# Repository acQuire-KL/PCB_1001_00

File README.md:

HISTORY

<table>
  <tr>
    <td valign="top">
      
    </td>
    <td valign="top">
      <table border="1">
        <tr>
          <th style="font-size: 14px; font-weight: bold;">VTPN</th>
          <th style="font-size: 14px; font-weight: bold;">Date</th>
          <th style="font-size: 14px; font-weight: bold;">Comments</th>
        </tr>
        <tr>
          <td style="font-size: 12px;">PCB_1001_02</td>
          <td style="font-size: 12px;">2025-04-02</td>
          <td style="font-size: 12px;">01 --> 02 rerouted to indepent circuits</td>
        </tr>
        <tr>
          <td style="font-size: 12px;">PCB_1001_01</td>
          <td style="font-size: 12px;">2025-03-28</td>
          <td style="font-size: 12px;">00 --> 01 to add new circuit sections</td>
        </tr>
        <tr>
          <td style="font-size: 12px;">PCB_1001_00</td>
          <td style="font-size: 12px;">2025-03-01</td>
          <td style="font-size: 12px;">Initial release</td>
        </tr>
      </table>
    </td>
  </tr>
</table>

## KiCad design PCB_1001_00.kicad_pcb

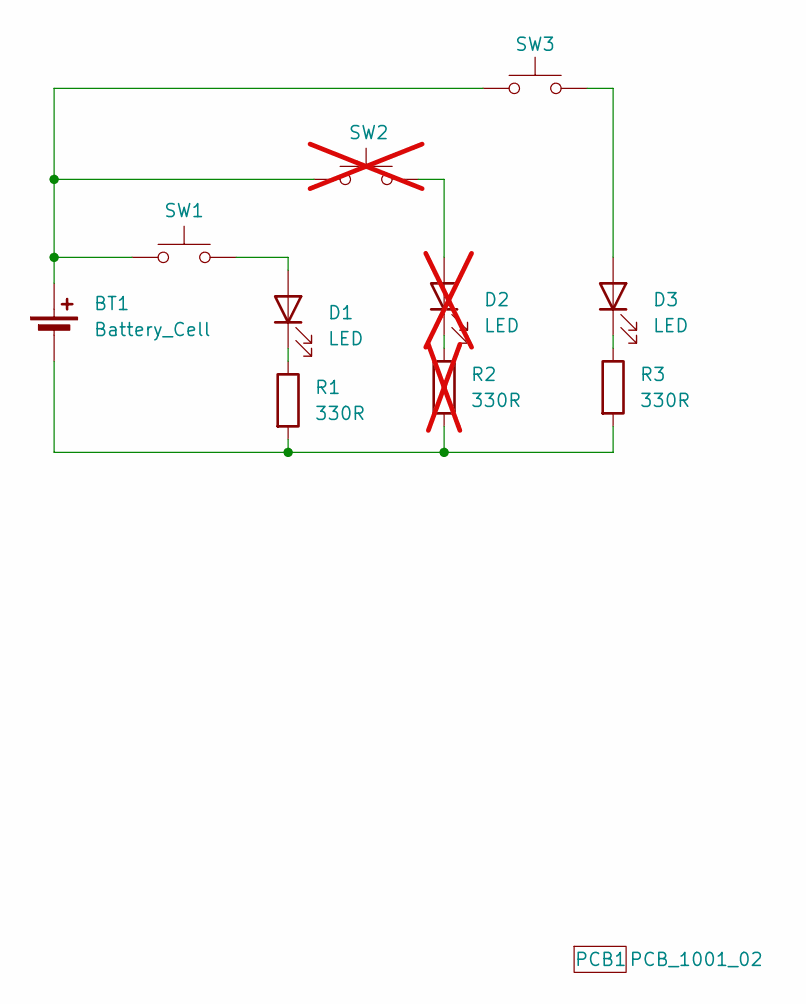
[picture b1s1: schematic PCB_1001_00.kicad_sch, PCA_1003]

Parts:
BT1: Battery_Cell; BatteryHolder_Keystone_1060_1x2032
D1, D3: LED; LED_0603_1608Metric
D2: LED; LED_0603_1608Metric; not fitted
PCB1: PCB_1001_02
R1, R3: 330R; R_0603_1608Metric
R2: 330R; R_0603_1608Metric; not fitted
SW1, SW3: SW_MEC_5G_edit; SW_Tactile_SPST_NO_Straight_CK_PTS636Sx25SMTRLFS
SW2: SW_MEC_5G_edit; SW_Tactile_SPST_NO_Straight_CK_PTS636Sx25SMTRLFS; not fitted

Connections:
unnamed: BT1.1 (+), SW1.1 (A), SW2.1 (A), SW3.1 (A)
unnamed: BT1.2 (-), R1.2, R2.2, R3.2
unnamed: D1.2 (A), SW1.2 (B)
unnamed: D1.1 (K), R1.1
unnamed: D2.2 (A), SW2.2 (B)
unnamed: D2.1 (K), R2.1
unnamed: D3.2 (A), SW3.2 (B)
unnamed: D3.1 (K), R3.1

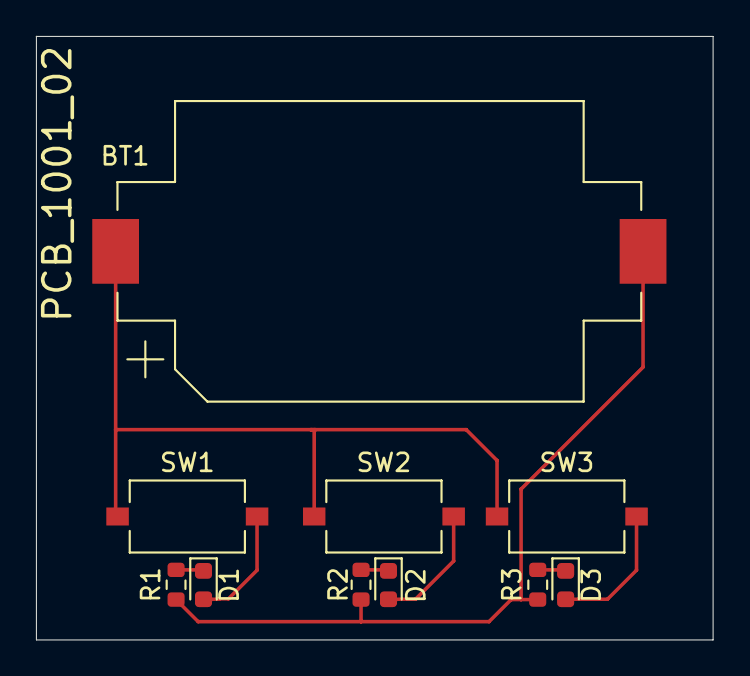
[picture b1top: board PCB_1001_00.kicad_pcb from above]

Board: 2 copper layers, 37.6 x 33.5 mm, 10 parts (0 on the bottom side), 8 nets.

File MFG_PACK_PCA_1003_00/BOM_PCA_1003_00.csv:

"Reference","Value","Datasheet","Footprint","Qty","DNP"
"BT1","Battery_Cell","~","Battery:BatteryHolder_Keystone_1060_1x2032","1",""
"D1,D3","LED","~","LED_SMD:LED_0603_1608Metric","2",""
"D2","LED","~","LED_SMD:LED_0603_1608Metric","1","DNP"
"R1,R3","330R","~","Resistor_SMD:R_0603_1608Metric","2",""
"R2","330R","~","Resistor_SMD:R_0603_1608Metric","1","DNP"
"SW1,SW3","SW_MEC_5G_edit","http://www.apem.com/int/index.php?controller=attachment&id_a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","Button_Switch_SMD:SW_Tactile_SPST_NO_Straight_CK_PTS636Sx25SMTRLFS","2",""
"SW2","SW_MEC_5G_edit","http://www.apem.com/int/index.php?controller=attachment&id_a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","Button_Switch_SMD:SW_Tactile_SPST_NO_Straight_CK_PTS636Sx25SMTRLFS","1","DNP"

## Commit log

2025-03-26 PCB_1001_00 Initialisation of Blank Project
2025-03-26 PCB_1001_00 with initial Schematic, Layout and 3D files
2025-03-26 PCB_1001_00 Layout was not part of the last commit
2025-03-26 VAR_PCA_1001_00 with LED set to DNP
2025-03-26 Gerber_PCB_1001_00 and VAR_PCA_1001_00 manufacturing files created
2025-03-26 Adding the Variant Schematic and Gerber Zip
2025-03-27 Fresh start with existing schematic and layout
2025-03-27 Deleting o/p files for a fresh start
2025-03-27 Deleting o/p (BOM.csv) files for a fresh start
2025-03-27 LED set back to Populate
2025-03-27 PCB -->01, 2 additional LED circuits
2025-03-27 Create README.md
    Initialised just with Top View image.
2025-03-27 Initialised README.md file
2025-03-28 PCB_1001_01 routing completed
2025-03-28 VAR_PCA_1001_00 Circuit #3 is DNP
2025-03-28 VAR_PCA_1002_00 circuit #2 & 3 is DNP
2025-03-28 Gerbers_PCB_1001_01 MFG Files
2025-03-29 Update README.md
    Changed image size and added descriptive table of changes.
2025-03-29 Gerbers, Schematic and BOM outputs created
2025-03-29 PCB_1001_00.kicad_pro fixed
2025-03-29 changed to exclude Autosave files
2025-03-30 PCB_1001_01 Gerber output generated
2025-03-31 Revert "VAR_PCA_1001_00 Circuit #3 is DNP"
2025-03-31 PCB_1001_01 Gerbers generated on Laptop
2025-03-31 Updated .gitignore file to stop auto save file
2025-04-01 PCA_1003_00 Initial Commit
2025-04-02 Gerbers_PCB_1001_02 creation
2025-04-02 Update README.md
    Reflect PCB_1001_02
2025-04-02 Changed Support Docs --> Support_Docs
2025-04-02 Updated file naming to remove spaces
2025-04-02 Update README.md
    Change to rev -02
2025-04-02 PCA_1003_01 update in progress. Need top add PCB as component
2025-04-02 prep sym_lib for adding PCB as schematic symbol
